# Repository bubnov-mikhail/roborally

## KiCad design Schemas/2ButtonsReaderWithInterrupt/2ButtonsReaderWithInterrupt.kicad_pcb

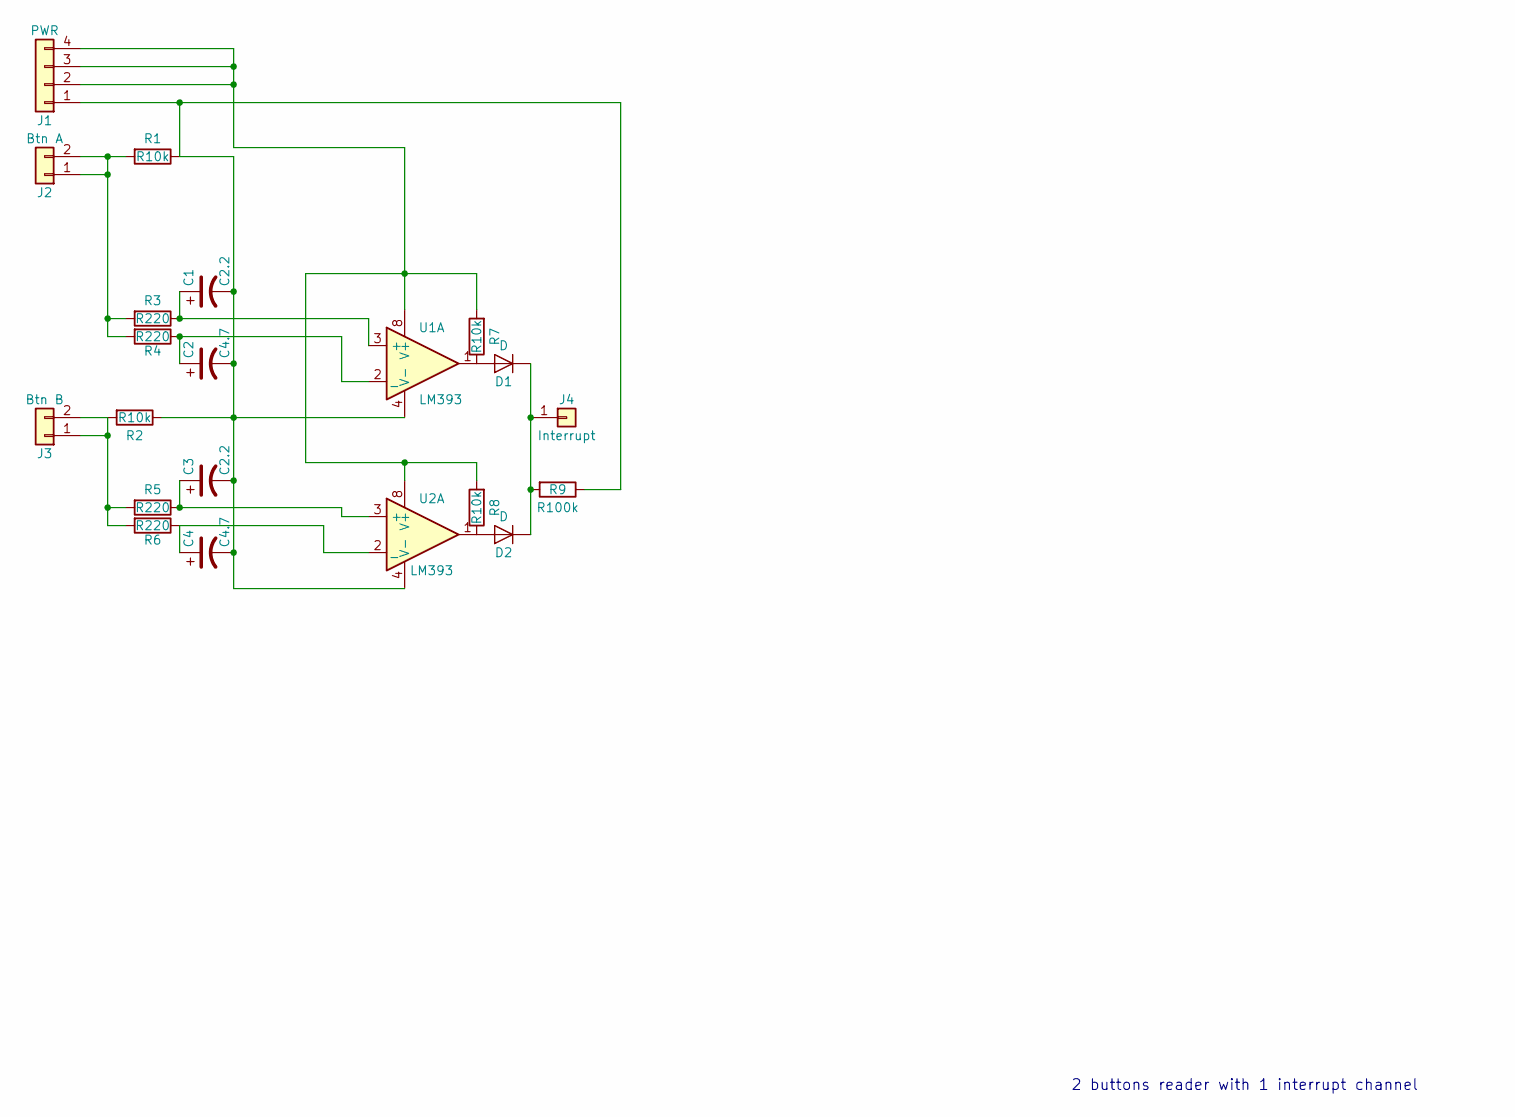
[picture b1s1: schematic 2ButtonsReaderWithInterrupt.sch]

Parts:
C1, C3: C2.2; CP_Radial_D5.0mm_P2.00mm
C2, C4: C4.7; CP_Radial_D5.0mm_P2.00mm
D1, D2: D; D_DO-41_SOD81_P10.16mm_Horizontal
J1: PWR; Socket_Strip_Straight_1x04_Pitch2.54mm
J2: Btn A; Socket_Strip_Straight_1x02_Pitch2.54mm
J3: Btn B; Socket_Strip_Straight_1x02_Pitch2.54mm
J4: Interrupt; Socket_Strip_Straight_1x01_Pitch2.54mm
R1, R2, R7, R8: R10k; R_Box_L13.0mm_W4.0mm_P9.00mm
R3, R4, R5, R6: R220; R_Box_L13.0mm_W4.0mm_P9.00mm
R9: R100k; R_Box_L13.0mm_W4.0mm_P9.00mm
U1, U2: LM393; DIP-8_W7.62mm

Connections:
unnamed: C1.1, R3.1, U1.3 (+)
unnamed: C1.2, C2.2, C3.2, C4.2, J1.1, R1.1, R2.1, R9.1, U1.4 (V-), U2.4 (V-)
unnamed: C2.1, R4.1, U1.2 (_)
unnamed: C3.1, R5.1, U2.3 (+)
unnamed: C4.1, R6.1, U2.2 (_)
unnamed: D1.1 (K), D2.1 (K), J4.1, R9.2
unnamed: D1.2 (A), R7.1, U1.1
unnamed: D2.2 (A), R8.1, U2.1
unnamed: J1.2, J1.3, J1.4, R7.2, R8.2, U1.8 (V+), U2.8 (V+)
unnamed: J2.1, J2.2, R1.2, R3.2, R4.2
unnamed: J3.1, J3.2, R2.2, R5.2, R6.2

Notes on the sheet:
2 buttons reader with 1 interrupt channel

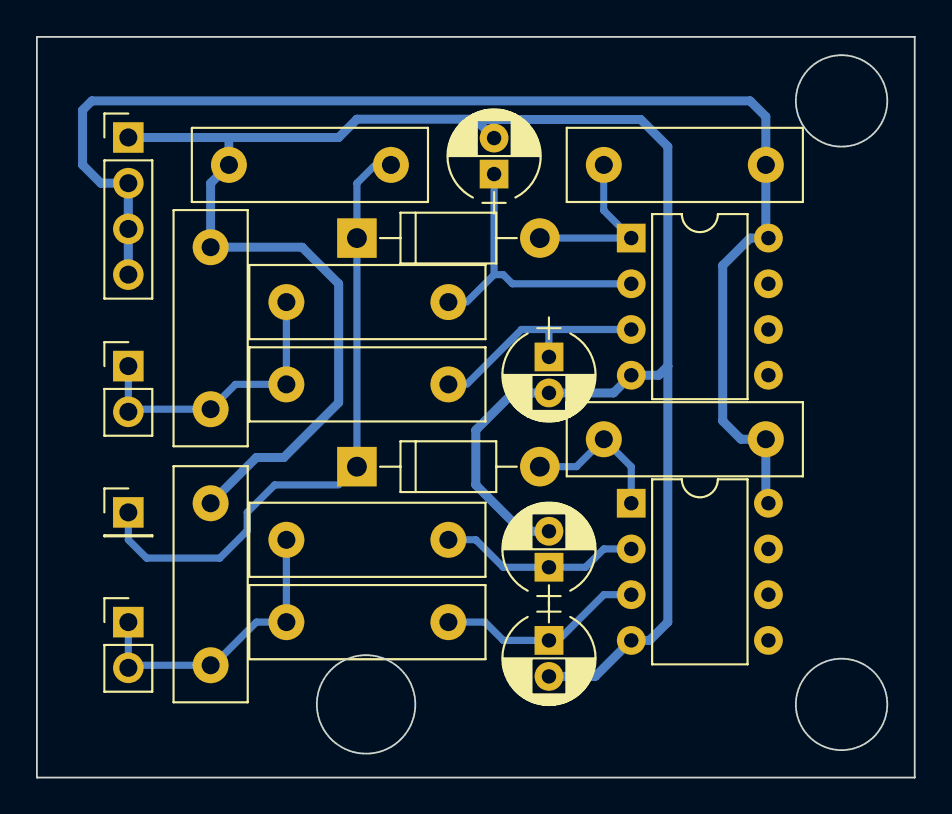
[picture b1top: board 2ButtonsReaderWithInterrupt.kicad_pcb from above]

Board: 2 copper layers, 48.8 x 41.1 mm, 21 parts (0 on the bottom side), 11 nets.

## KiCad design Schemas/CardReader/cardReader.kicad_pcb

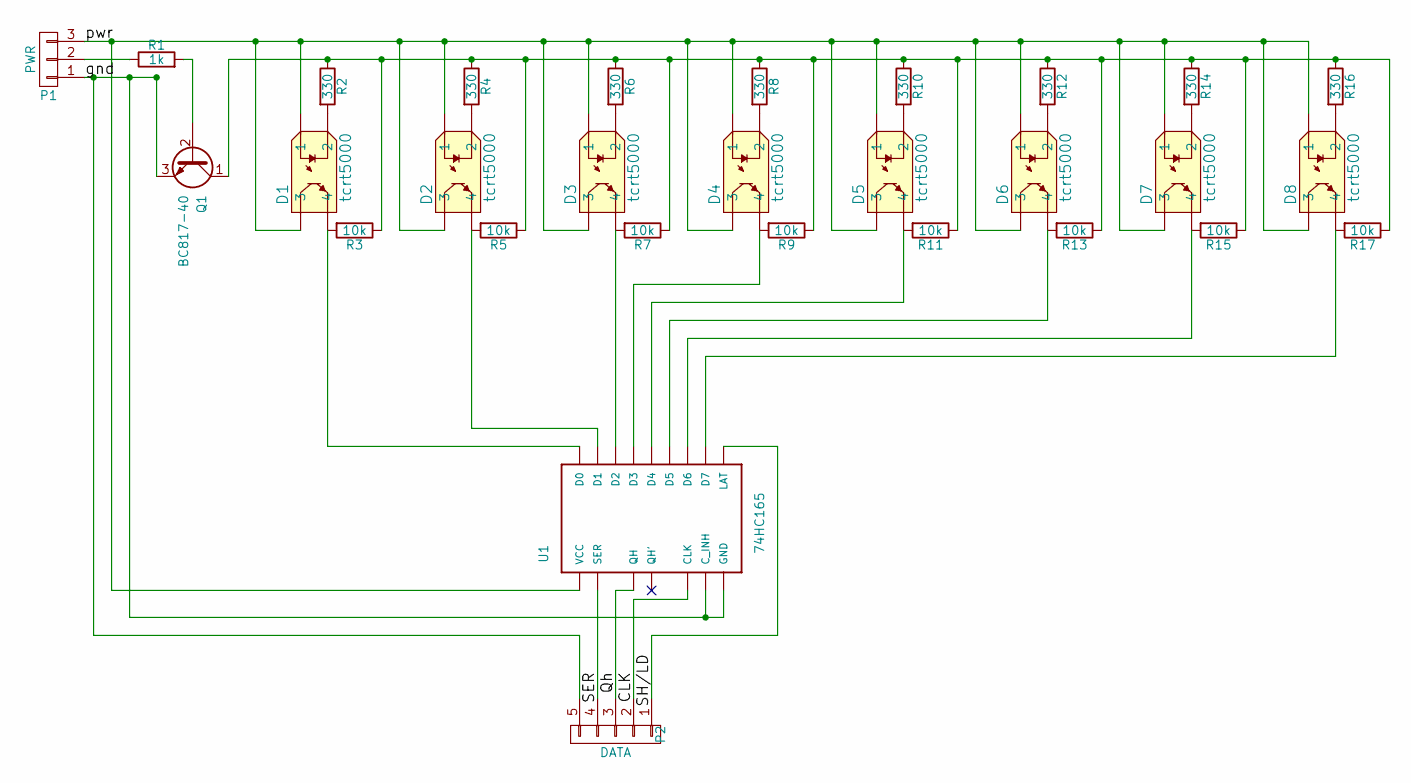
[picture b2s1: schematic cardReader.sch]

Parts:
D1, D2, D3, D4, D5, D6, D7, D8: tcrt5000; TCRT5000
P1: PWR; Pin_Header_Straight_1x03_Pitch2.54mm
P2: DATA; Pin_Header_Straight_1x05_Pitch2.54mm
Q1: BC817-40; TO-92_Inline_Wide
R1: 1k; R_Axial_DIN0207_L6.3mm_D2.5mm_P7.62mm_Horizontal
R2, R4, R6, R8, R10, R12, R14, R16: 330; R_Axial_DIN0207_L6.3mm_D2.5mm_P7.62mm_Horizontal
R3, R5, R7, R9, R11, R13, R15, R17: 10k; R_Axial_DIN0207_L6.3mm_D2.5mm_P7.62mm_Horizontal
U1: 74HC165; DIP-16_W7.62mm

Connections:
/CLK: P2.2, U1.2 (CLK)
/Qh: P2.3, U1.9 (QH)
/SER: P2.4, U1.10 (SER)
/SH/LD: P2.1, U1.1 (LAT)
/gnd: P1.1, P2.5, Q1.3 (E), U1.8 (GND), U1.15 (C_INH)
/pwr: D1.1, D1.3, D2.1, D2.3, D3.1, D3.3, D4.1, D4.3, D5.1, D5.3, D6.1, D6.3, D7.1, D7.3, D8.1, D8.3, P1.3, U1.16 (VCC)
unnamed: D1.2, R2.2
unnamed: D1.4, R3.2, U1.11 (D0)
unnamed: D2.2, R4.2
unnamed: D2.4, R5.2, U1.12 (D1)
unnamed: D3.2, R6.2
unnamed: D3.4, R7.2, U1.13 (D2)
unnamed: D4.2, R8.2
unnamed: D4.4, R9.2, U1.14 (D3)
unnamed: D5.2, R10.2
unnamed: D5.4, R11.2, U1.3 (D4)
unnamed: D6.2, R12.2
unnamed: D6.4, R13.2, U1.4 (D5)
unnamed: D7.2, R14.2
unnamed: D7.4, R15.2, U1.5 (D6)
unnamed: D8.2, R16.2
unnamed: D8.4, R17.2, U1.6 (D7)
unnamed: P1.2, R1.1
unnamed: Q1.1 (C), R2.1, R3.1, R4.1, R5.1, R6.1, R7.1, R8.1, R9.1, R10.1, R11.1, R12.1, R13.1, R14.1, R15.1, R16.1, R17.1
unnamed: Q1.2 (B), R1.2

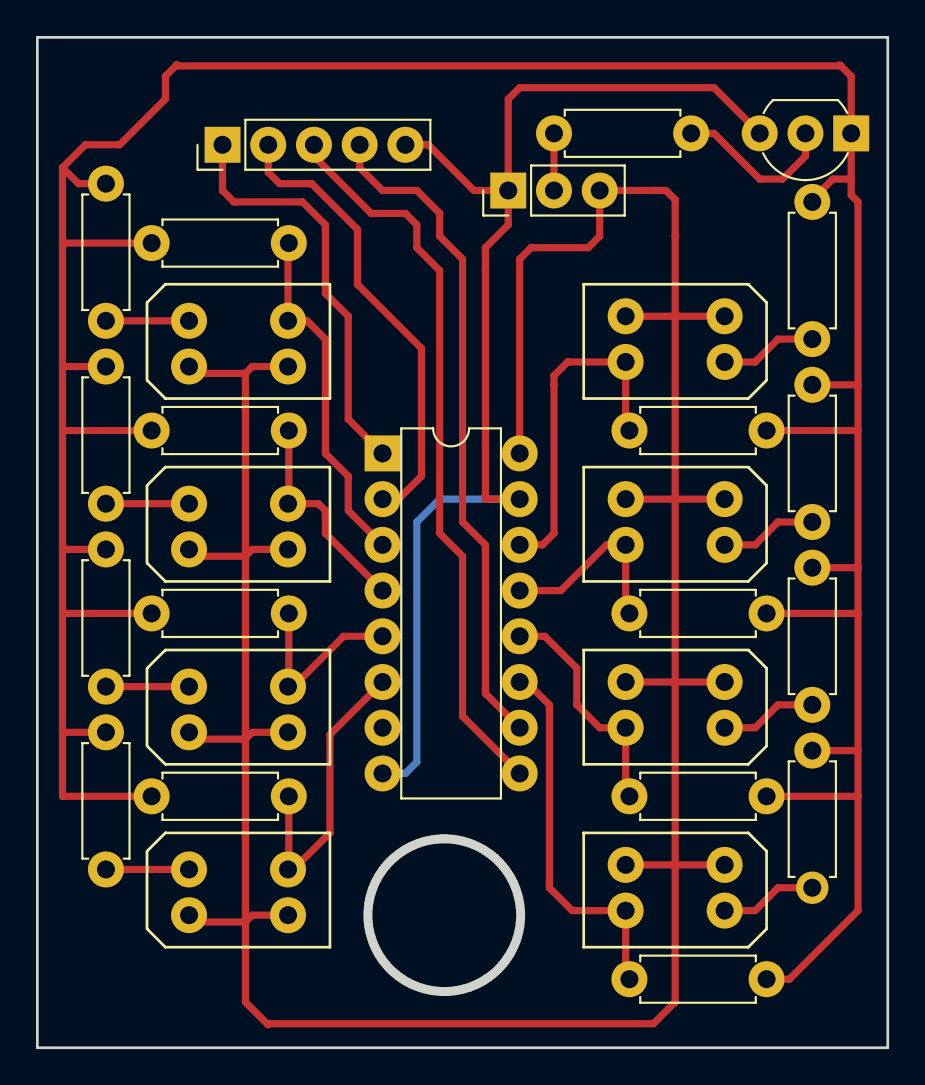
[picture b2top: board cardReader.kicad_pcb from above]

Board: 2 copper layers, 46.9 x 55.8 mm, 29 parts (0 on the bottom side), 25 nets.

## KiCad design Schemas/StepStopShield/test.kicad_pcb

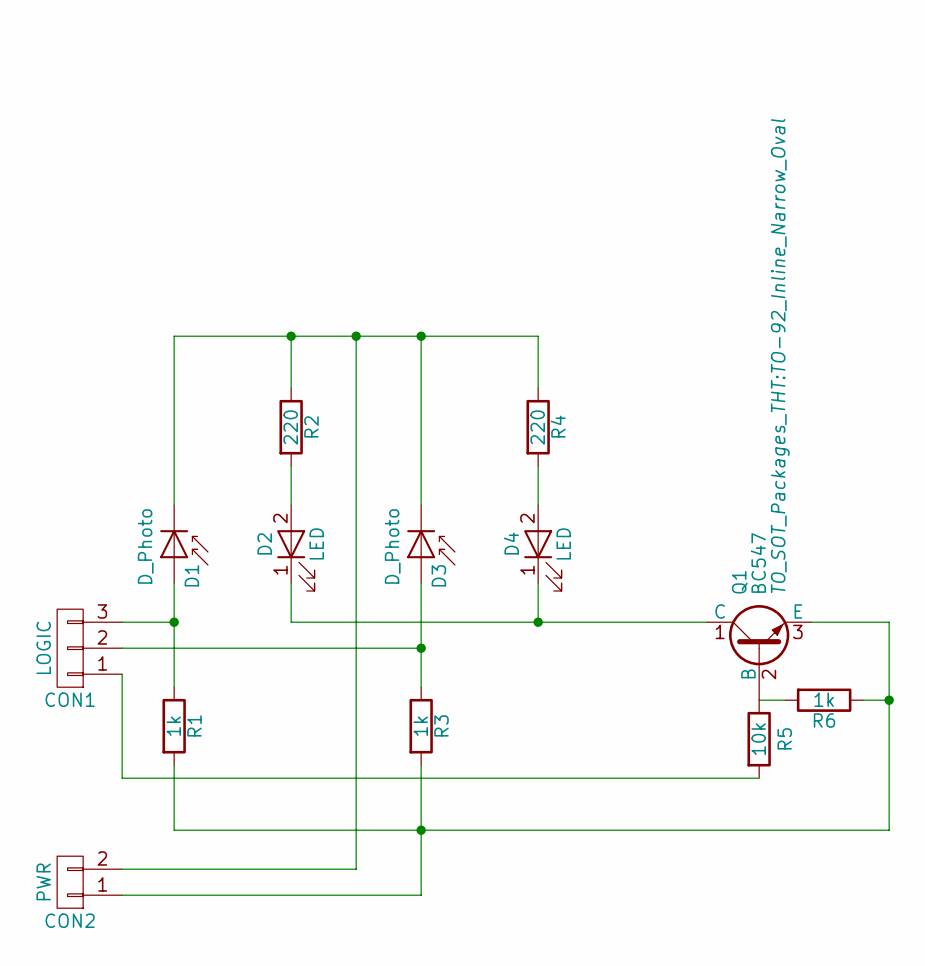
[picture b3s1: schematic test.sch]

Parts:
CON1: LOGIC; Socket_Strip_Straight_1x03
CON2: PWR; Socket_Strip_Straight_1x02
D1, D3: D_Photo; LED_D3.0mm
D2, D4: LED; LED_D3.0mm
Q1: BC547; TO-92_Inline_Narrow_Oval
R1, R3: 1k; R_Axial_DIN0207_L6.3mm_D2.5mm_P10.16mm_Horizontal
R2, R4: 220; R_Axial_DIN0207_L6.3mm_D2.5mm_P10.16mm_Horizontal
R5: 10k; R_Axial_DIN0207_L6.3mm_D2.5mm_P10.16mm_Horizontal
R6: 1k; R_Axial_DIN0309_L9.0mm_D3.2mm_P12.70mm_Horizontal

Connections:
unnamed: CON1.1, R5.2
unnamed: CON1.2, D3.2 (A), R3.1
unnamed: CON1.3, D1.2 (A), R1.1
unnamed: CON2.1, Q1.3 (E), R1.2, R3.2, R6.1
unnamed: CON2.2, D1.1 (K), D3.1 (K), R2.1, R4.1
unnamed: D2.1 (K), D4.1 (K), Q1.1 (C)
unnamed: D2.2 (A), R2.2
unnamed: D4.2 (A), R4.2
unnamed: Q1.2 (B), R5.1, R6.2

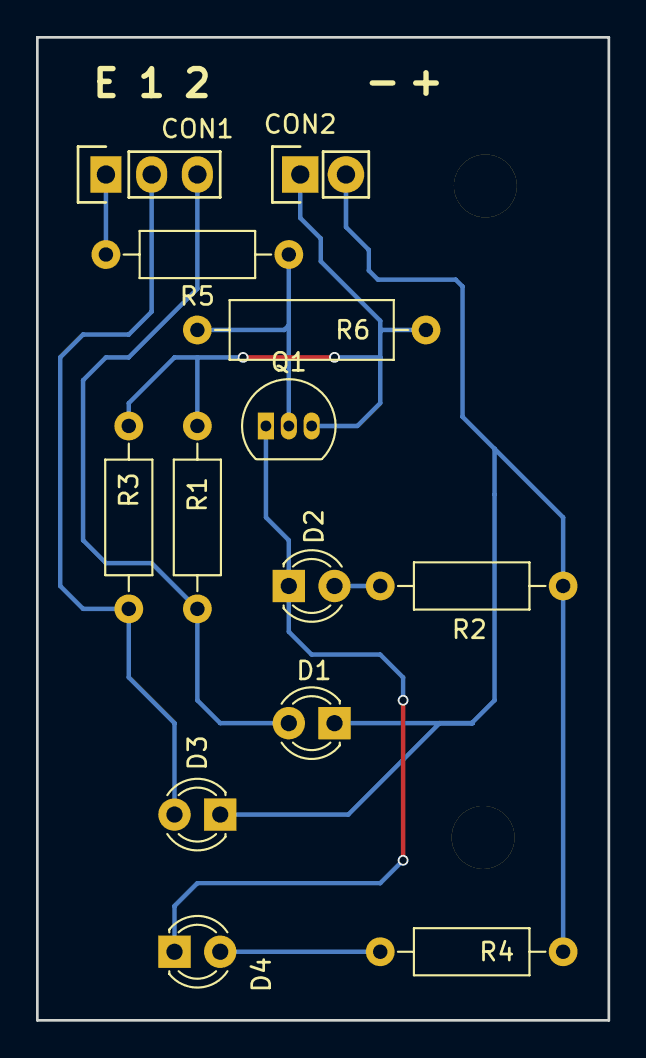
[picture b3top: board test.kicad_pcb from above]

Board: 2 copper layers, 31.8 x 54.6 mm, 15 parts (0 on the bottom side), 9 nets.

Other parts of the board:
H1, H1#2: MountingHole_3.5mm

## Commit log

2016-11-11 init
2016-11-11 Update start msg
2016-11-11 Add execCommandEvent
2016-11-11 Test it there is no current programm
2016-11-11 Complete communication master <> motorSlave
    Add env in platformio.ini
2016-11-15 Add Schemas/*
2016-11-16 add light sensor schema
2016-11-17 Add lib_dep for Adafruit motor shield lib
    Add Include in motorSlave
2016-11-17 Add STATE_CALIBRATING
    Move function deffinitions to motorSlave.h
2016-11-17 Add motorSlave.h
2016-11-17 Add calibratng function with tests
2016-11-21 Add main.cpp
    Add main::handleFatalError
2016-11-21 Add main.h
    Add main::handleFatalError
2016-11-21 Add MotorAxis
2016-11-21 Add MotorAxis
    Complete motorSlave
2016-11-21 Add include <AFMotor.h> in motorSlave.cpp
2016-11-23 Remove include <AFMotor.h> from MotorAxis.cpp
2016-11-23 Move #include <Arduino.h> from MotorAxis.cpp to MotorAxis.h
2016-11-23 Add DataBus class
    Use it in main.cpp
    Also rename INTERRUPT_PIN to MAIN_INTERRUPT_PIN and MOTOR_SLAVE_INTERRUPT_PIN
2016-11-24 Add TCRT5000
    Схема подключения IK оптопары
2016-11-24 Add main bus to device schema
2016-11-24 Update MotorAxis.cpp and .h
    Set FULL_SPEED to 255 and HALF_SPEED to 128
    Rotate RELEASE and BRAKE, end with BRAKE
    Add some usefull comments
2016-11-24 Update main.cpp::handleFatalError()
2016-11-24 Update motorSlave.cpp and .h
    Redefine STOP/STEP pins
    pinMode for interrup changed from INPUT_PULLUP to INPUT
2016-11-25 Add pulse schema for interrupt bus
2016-11-25 periodically flashing LED
2016-11-25 Update pulse_schema_for_interrupt_bus
2016-11-25 Add label XOR to Pulse_schema_for_interrupt_bus.png
2016-11-25 Another try
2016-12-11 Add test.cpp
2016-12-11 Rename test.cpp to testInterruptPulse.cpp
    Add some comments
2016-12-18 Remove testInterrptPulse.cpp
2016-12-27 Add test.cpp with ir sensor reader test
2016-12-29 Do not use interrupts in motorSlave
2016-12-29 Update test.cpp - do not trigger latch
    Set it LOW, read, then set it HIGH
2016-12-29 Update DataBus::getDeviceData
    Trigger LOW and back to HIGH
2016-12-29 Update test.cpp
    include <Print.h> to use type in Serial.println
2017-01-12 Update MotorAxis.cpp
    use digitalRead (inverted) instead of analogRead
2017-01-12 Fix motorSlave.cpp and .h
    Fix condition in checkPins()
    Change pins
2017-01-15 Complete motorSlave
2017-01-16 Move AF_DCMotor and MotorAxis definition
    Into doExecuteCommand
2017-02-03 Add kicad schema
2017-02-06 Complete motorSlave movement
2017-02-08 Add cardReader schema
2017-02-09 Update cardReader schema, add end pin
2017-02-09 minor updates to cardReader schema
2017-02-09 Fix test.cpp
2017-09-30 Set lib_ldf_mode in platformio.ini
2017-09-30 Update test.cpp for testing 2 buttons interruption
2017-10-01 Add 2ButtonsReaderWithInterrupt
2017-10-11 Add #pragma once to lib/*.hpp
2017-10-11 Add a pull down resistor
2017-10-11 Fix test.cpp, change interrupt condition
2017-10-18 Change 2ButtonsReaderWithInterrupt schema
2017-10-18 Add schema
2017-10-19 Update 2ButtonsReaderWithInterrupt, remove layout/
2017-10-31 Clear the test.cpp
2017-10-31 Fix DatBus lib
2017-10-31 Test DataBus output
2017-11-10 Add button2interrupt on npn schema
2019-05-02 Update platformio.ini, change dep on AFMotor
